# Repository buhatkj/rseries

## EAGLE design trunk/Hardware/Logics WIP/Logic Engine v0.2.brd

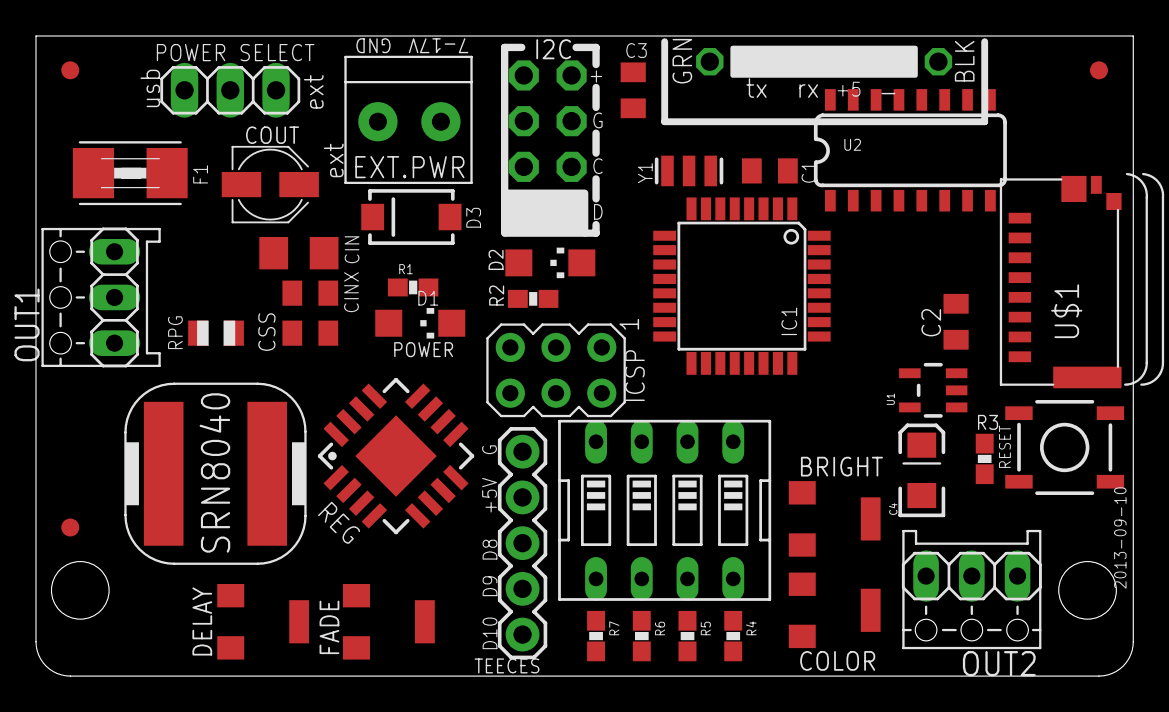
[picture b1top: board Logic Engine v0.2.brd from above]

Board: 2 copper layers, 61.0 x 35.6 mm, 45 parts (0 on the bottom side), 44 nets, no tracks yet.

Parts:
BRIGHT: 3364
C1, C2, C3: 0.1uF; C0805K
C4: 10uF; EIA3216
CIN: 10uF; C1206
CINX: 100nF; C0805K
COLOR: 3364
COUT: 22uF; CASE_B
CSS: 3.3nF; C0805K
D1: CHIPLED_1206
D2: Green; CHIPLED_1206
D3: BA340LA; SMA-DIODE
DELAY: 3364
EXT.PWR: 1X2-3.5MM
F1: 1812
FADE: 3364
FID1, FID2, FID3: FIDUCIAL1X2.5; FIDUCIAL-1X2.5
FTDI: 1X06-CLEAN
I2C, I2C1: 1X04-CB
IC1: MEGA328P; TQFP32-08
ICSP: AVRISP-6; AVRISP
INDUCTOR: SRN8040-2R2Y; SRN8040
OUT1, OUT2: MDF7_1X03
PWR_SEL1: 1X03
R1, R2: 1K; 0603-RES
R3, R4, R5, R6, R7: 10K; 0603-RES
REG: TPS62133; TPS6213X
RESET: TACTILE_SWITCH_SMD
RPG: 100k; R0805
SW1: EDG-04
TEECES: 1X05
U1: V_REG_LDOSMD; SOT23-5
U2: HEX_CONVERTER; SO016
U$1: MICROSD; MICROSD_SMALL
Y1: 16MHz; RESONATOR-SMD

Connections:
+5V: BRIGHT.3, C1.1, C2.1, COLOR.3, DELAY.3, F1.1, FADE.3, I2C.4, I2C1.4, IC1.4, IC1.6, IC1.18, ICSP.2, OUT1.2, OUT2.2, R1.1, R3.1, TEECES.2, U1.1, U1.3, U$1.4
ANALOG0: DELAY.2, IC1.23
ANALOG1: FADE.2, IC1.24
ANALOG2: BRIGHT.2, IC1.25
ANALOG3: COLOR.2, IC1.26
ANALOG4: I2C.1, I2C1.1, IC1.27
ANALOG5: I2C.2, I2C1.2, IC1.28
DIGITAL2: IC1.32, SW1.1
DIGITAL3: IC1.1, SW1.2
DIGITAL4: IC1.2, SW1.3
DIGITAL5: IC1.9, SW1.4
DIGITAL6: IC1.10, OUT1.1, OUT2.1
DIGITAL7: IC1.11, TEECES.5
DIGITAL8: IC1.12, TEECES.3
DIGITAL9: IC1.13, TEECES.4
DIGITAL10: IC1.14, U2.3
GND: BRIGHT.1, C1.2, C2.2, C4.C, CIN.2, CINX.2, COLOR.1, COUT.-, CSS.2, D1.C, D2.C, DELAY.1, EXT.PWR.1, FADE.1, FTDI.1, FTDI.2, I2C.3, I2C1.3, IC1.3, IC1.5, IC1.21, ICSP.6, OUT1.3, OUT2.3, R4.2, R5.2, R6.2, R7.2, REG.5, REG.6, REG.8, REG.15, REG.16, REG.17-THERMALPAD, RESET.3, TEECES.1, U1.2, U2.8, U$1.6, U$1.MT1, U$1.MT2, Y1.2
MISO: IC1.16, ICSP.1, U$1.7
MOSI: IC1.15, ICSP.4, U2.5
unnamed: IC1.7, Y1.1
unnamed: IC1.8, Y1.3
unnamed: INDUCTOR.P$1, REG.1
unnamed: D2.A, R2.2
unnamed: D1.A, R1.2
unnamed: CIN.1, CINX.1, D3.C, REG.10, REG.11, REG.12, REG.13
unnamed: CSS.1, REG.9
unnamed: REG.4, RPG.2
unnamed: COUT.+, INDUCTOR.P$2, PWR_SEL1.1, REG.7, REG.14, RPG.1
unnamed: F1.2, PWR_SEL1.2
unnamed: D3.A, EXT.PWR.2
unnamed: R4.1, SW1.8
unnamed: R5.1, SW1.7
unnamed: R6.1, SW1.6
unnamed: R7.1, SW1.5
unnamed: U2.4, U$1.3
unnamed: U2.6, U$1.5
unnamed: U2.2, U$1.2
unnamed: C4.A, U1.5, U2.1
RST: C3.2, IC1.29, ICSP.5, R3.2, RESET.1
RTS#: C3.1, FTDI.6
RXD: FTDI.4, IC1.30
SCK: IC1.17, ICSP.3, R2.1, U2.7
TXD: FTDI.5, IC1.31
USB_5V: FTDI.3, PWR_SEL1.3

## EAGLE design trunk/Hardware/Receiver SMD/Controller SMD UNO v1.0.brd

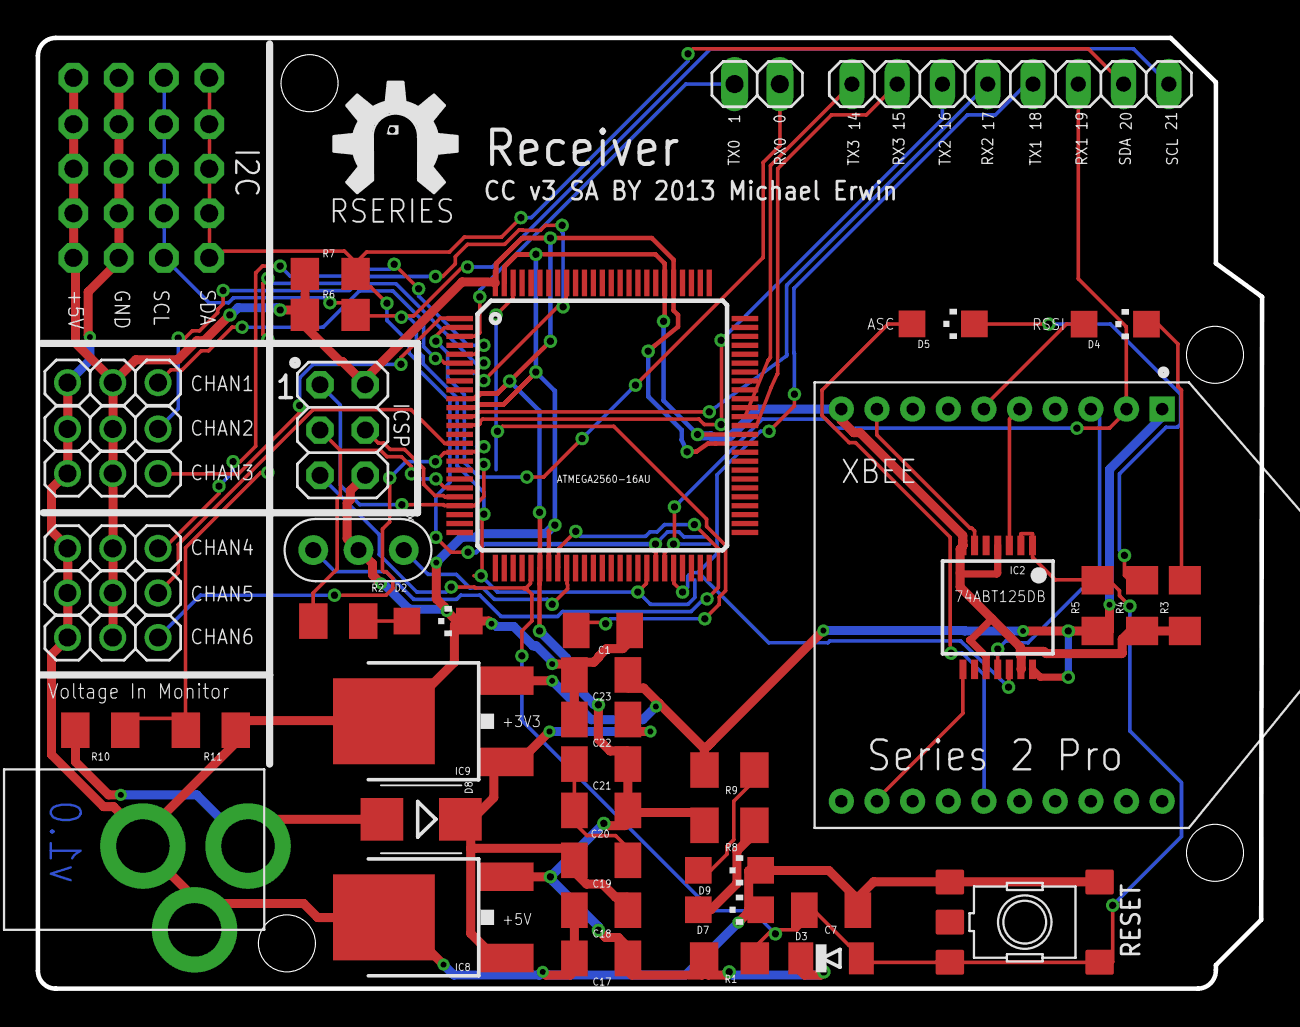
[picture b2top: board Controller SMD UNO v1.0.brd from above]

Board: 2 copper layers, 68.7 x 53.3 mm, 51 parts (1 on the bottom side), 41 nets.

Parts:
C1, C17, C18, C21, C23: 0.1uF; C1206K
C7: 22p; C1206K
C19, C20, C22: 10uf 25V; C1206K
CHAN1, CHAN2, CHAN3, CHAN4, CHAN5, CHAN6: 1X03
COMMUNICATION: 8x1F-H8.5; 1X08
D2: RED; CHIPLED_1206
D3: CD1206-S01575; MINIMELF
D4, D5, D7, D9: CHIPLED_1206
D8: SMB
I2C, I2C1, I2C2, I2C3, I2C4: 1X04-CB
IC2: 74ABT125DB; SSOP14
IC3: ATMEGA2560-16AU; TQFP100
IC8, IC9: LM2931_FIXED; DPAK
ICSP: 3x2M; 2X03
J2: 2.1MMJACK; PJ-102A
JP1: 1X02
R1, R5, R6, R7: 10K; R1206
R2, R8, R9: 1.0 K; M1206
R3, R4: 1K; R1206
R10: 47.0 K; M1206
R11: 24.0 K; M1206
RESET: TS42031-160R-TR-7260; TS42
U$1: ROYAL-ENGINEERS-OF-NABOO
U$3: RSERIES-OSHW-LOGO; RSERIES-OSHW-LOGO-LARGE
X1: 16.00MHz; CERM_OSC
XBEE: XBEE

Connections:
+5V: C17.1, C20.1, C21.1, CHAN1.2, CHAN2.2, CHAN3.2, CHAN4.2, CHAN5.2, CHAN6.2, D3.C, I2C.4, I2C1.4, I2C2.4, I2C3.4, I2C4.4, IC3.10, IC3.31, IC3.61, IC3.80, IC3.100, IC8.3, ICSP.2, R1.1, R6.2, R7.2, R8.1
+9V: C18.1, C19.1, C22.1, D8.C, IC8.1, IC9.1
ADC5: IC3.92, R10.1, R11.2
AREF: C1.1, IC3.98
GND: C1.2, C7.2, C17.2, C18.2, C22.2, C23.2, CHAN1.3, CHAN2.3, CHAN3.3, CHAN4.3, CHAN5.3, CHAN6.3, D2.C, D7.C, D9.C, I2C.3, I2C1.3, I2C2.3, I2C3.3, I2C4.3, IC2.4, IC2.7, IC2.10, IC2.13, IC3.11, IC3.32, IC3.62, IC3.81, IC3.99, IC8.4, IC9.4, ICSP.6, J2.RING, J2.RING_SW, R3.1, R4.1, R11.1, RESET.1, RESET.2, X1.P$2, XBEE.10
unnamed: IC2.11, XBEE.3
unnamed: D5.C, R4.2
unnamed: D4.A, XBEE.6
unnamed: D4.C, R3.2
unnamed: D9.A, R9.2
unnamed: IC2.6, XBEE.9
unnamed: D2.A, R2.1
unnamed: IC2.3, XBEE.5
unnamed: IC2.8, XBEE.12
unnamed: D5.A, XBEE.15
unnamed: D7.A, R8.2
unnamed: D8.A, J2.TIP, R10.2
unnamed: C19.2, C20.2, C21.2
PB1: IC3.20, ICSP.3, R2.2
PB2: IC3.21, ICSP.4
PB3: IC3.22, ICSP.1
PE0: IC3.2, JP1.1
PE1: IC3.3, JP1.2
PE3: CHAN4.1, IC3.5
PE4: CHAN1.1, IC3.6
PE5: CHAN2.1, IC3.7
PG5: CHAN3.1, IC3.1
PH3: CHAN5.1, IC3.15
PH4: CHAN6.1, IC3.16
RESET: C7.1, D3.A, IC2.1, IC2.2, IC3.30, ICSP.5, R1.2, R5.2, RESET.3, RESET.4
RXD1: COMMUNICATION.3, IC3.45, XBEE.2
RXD2: COMMUNICATION.5, IC3.12
RXD3: COMMUNICATION.7, IC3.63
SCL: COMMUNICATION.1, I2C.2, I2C1.2, I2C2.2, I2C3.2, I2C4.2, IC3.43, R6.1
SDA: COMMUNICATION.2, I2C.1, I2C1.1, I2C2.1, I2C3.1, I2C4.1, IC3.44, R7.1
TXD1: COMMUNICATION.4, IC2.12, IC3.46
TXD2: COMMUNICATION.6, IC3.13
TXD3: COMMUNICATION.8, IC3.64
VCC: C23.1, IC2.14, IC9.3, R5.1, R9.1, XBEE.1
XTAL1: IC3.34, X1.P$3
XTAL2: IC3.33, X1.P$1

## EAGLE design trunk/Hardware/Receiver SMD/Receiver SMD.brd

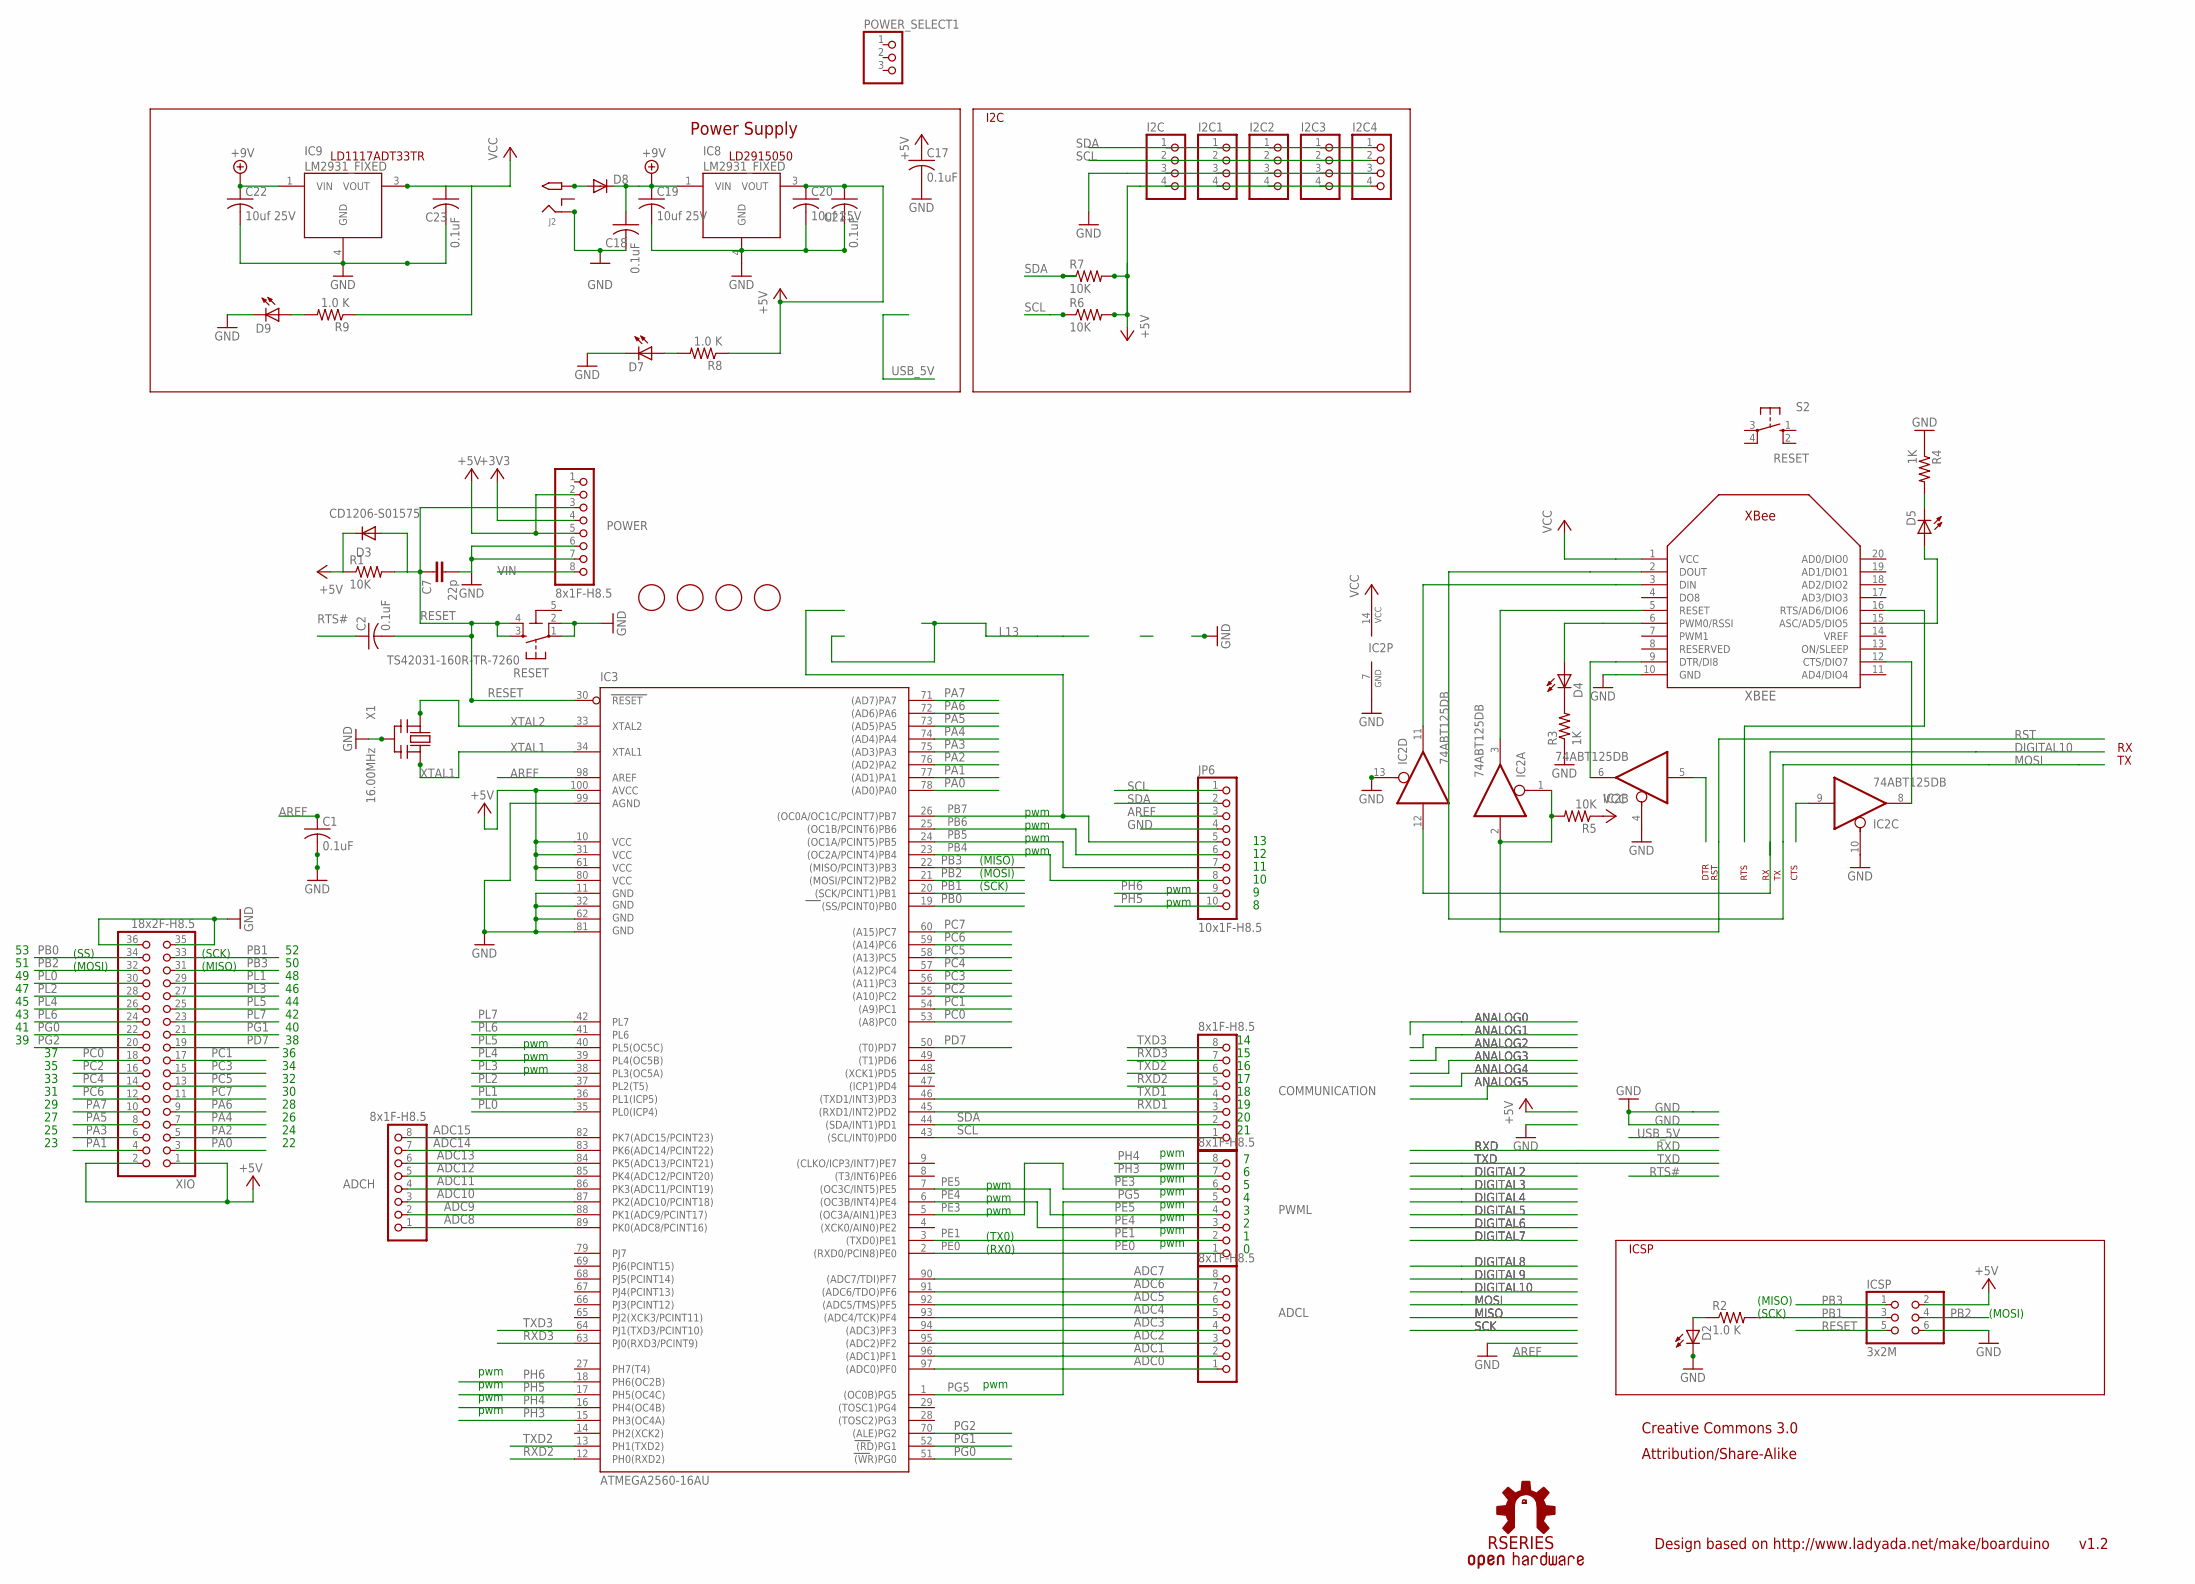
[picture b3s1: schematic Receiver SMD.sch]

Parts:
ADCH: 8x1F-H8.5; 1X08
ADCL: 8x1F-H8.5; 1X08
C1, C2, C17, C18, C21, C23: 0.1uF; C1206K
C7: 22p; C0603-ROUND
C19, C20, C22: 10uf 25V; C1206K
COMMUNICATION: 8x1F-H8.5; 1X08
D2: RED; CHIPLED_1206
D3: CD1206-S01575; MINIMELF
D4, D5, D7, D9: LEDCHIPLED_1206; CHIPLED_1206
D8: DIODE-SMB; SMB
FD1, FD2, FD3, FD4: FIDUCIALMOUNT; FIDUCIA-MOUNT
I2C, I2C1, I2C2, I2C3, I2C4: PINHD-1X4CB; 1X04-CB
IC2: 74ABT125DB; SSOP14
IC3: ATMEGA2560-16AU; TQFP100
IC8, IC9: LM2931_FIXED; DPAK
ICSP: 3x2M; 2X03
J2: 2.1MMJACK; PJ-102A
JP6: 10x1F-H8.5; 1X10
POWER: 8x1F-H8.5; 1X08
POWER_SELECT1: PINHD-1X3; 1X03
PWML: 8x1F-H8.5; 1X08
R1, R5, R6, R7: 10K; R1206
R2, R8, R9: 1.0 K; M1206
R3, R4: 1K; R1206
RESET: TS42031-160R-TR-7260; TS42
S2: RESET; B3F-10XX
U$6: RSERIES-OSHW-LOGOMEDIUM; RSERIES-OSHW-LOGO-MEDIUM
X1: 16.00MHz; CERM_OSC
XBEE: XBEE
XIO: 18x2F-H8.5; 2X18

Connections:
5-GND: RESET.5 (5-GND)
+3V3: POWER.4
+5V: C17.1, C20.1, C21.1, D3.C, I2C.4, I2C1.4, I2C2.4, I2C3.4, I2C4.4, IC3.10 (VCC), IC3.31 (VCC1), IC3.61 (VCC2), IC3.80 (VCC3), IC3.100 (AVCC), IC8.3 (VOUT), ICSP.2, POWER.2, POWER.5, R1.1, R6.2, R7.2, R8.1, XIO.1, XIO.2
+9V: C18.1, C19.1, C22.1, D8.C, IC8.1 (VIN), IC9.1 (VIN)
ADC0: ADCL.1, IC3.97 ((ADC0)PF0)
ADC1: ADCL.2, IC3.96 ((ADC1)PF1)
ADC2: ADCL.3, IC3.95 ((ADC2)PF2)
ADC3: ADCL.4, IC3.94 ((ADC3)PF3)
ADC4: ADCL.5, IC3.93 ((ADC4/TCK)PF4)
ADC5: ADCL.6, IC3.92 ((ADC5/TMS)PF5)
ADC6: ADCL.7, IC3.91 ((ADC6/TDO)PF6)
ADC7: ADCL.8, IC3.90 ((ADC7/TDI)PF7)
ADC8: ADCH.1, IC3.89 (PK0(ADC8/PCINT16))
ADC9: ADCH.2, IC3.88 (PK1(ADC9/PCINT17))
ADC10: ADCH.3, IC3.87 (PK2(ADC10/PCINT18))
ADC11: ADCH.4, IC3.86 (PK3(ADC11/PCINT19))
ADC12: ADCH.5, IC3.85 (PK4(ADC12/PCINT20))
ADC13: ADCH.6, IC3.84 (PK5(ADC13/PCINT21))
ADC14: ADCH.7, IC3.83 (PK6(ADC14/PCINT22))
ADC15: ADCH.8, IC3.82 (PK7(ADC15/PCINT23))
AREF: C1.1, IC3.98 (AREF), JP6.3
DIGITAL10: IC2.12 (I)
GND: C1.2, C7.2, C17.2, C18.2, C22.2, C23.2, D2.C, D7.C, D9.C, I2C.3, I2C1.3, I2C2.3, I2C3.3, I2C4.3, IC2.4 (OE), IC2.7 (GND), IC2.10 (OE), IC2.13 (OE), IC3.11 (GND), IC3.32 (GND1), IC3.62 (GND2), IC3.81 (GND3), IC3.99 (AGND), IC8.4 (GND), IC9.4 (GND), ICSP.6, J2.RING, JP6.4, POWER.6, POWER.7, R3.1, R4.1, RESET.1, RESET.2, X1.P$2 (GND), XBEE.10 (GND), XIO.35, XIO.36
MOSI: XBEE.2 (DOUT)
unnamed: IC2.11 (O), XBEE.3 (DIN)
unnamed: D5.C, R4.2
unnamed: D4.A, XBEE.6 (PWM0/RSSI)
unnamed: D4.C, R3.2
unnamed: D9.A, R9.2
unnamed: IC2.6 (O), XBEE.9 (DTR/DI8)
unnamed: D2.A, R2.1
unnamed: IC2.3 (O), XBEE.5 (RESET)
unnamed: IC2.8 (O), XBEE.12 (CTS/DIO7)
unnamed: D5.A, XBEE.15 (ASC/AD5/DIO5)
unnamed: D7.A, R8.2
unnamed: D8.A, J2.TIP
unnamed: C19.2, C20.2, C21.2
PA0: IC3.78 ((AD0)PA0), XIO.3
PA1: IC3.77 ((AD1)PA1), XIO.4
PA2: IC3.76 ((AD2)PA2), XIO.5
PA3: IC3.75 ((AD3)PA3), XIO.6
PA4: IC3.74 ((AD4)PA4), XIO.7
PA5: IC3.73 ((AD5)PA5), XIO.8
PA6: IC3.72 ((AD6)PA6), XIO.9
PA7: IC3.71 ((AD7)PA7), XIO.10
PB0: IC3.19 ((SS/PCINT0)PB0), XIO.34
PB1: IC3.20 ((SCK/PCINT1)PB1), ICSP.3, R2.2, XIO.33
PB2: IC3.21 ((MOSI/PCINT2)PB2), ICSP.4, XIO.32
PB3: IC3.22 ((MISO/PCINT3)PB3), ICSP.1, XIO.31
PB4: IC3.23 ((OC2A/PCINT4)PB4), JP6.8
PB5: IC3.24 ((OC1A/PCINT5)PB5), JP6.7
PB6: IC3.25 ((OC1B/PCINT6)PB6), JP6.6
PB7: IC3.26 ((OC0A/OC1C/PCINT7)PB7), JP6.5
PC0: IC3.53 ((A8)PC0), XIO.18
PC1: IC3.54 ((A9)PC1), XIO.17
PC2: IC3.55 ((A10)PC2), XIO.16
PC3: IC3.56 ((A11)PC3), XIO.15
PC4: IC3.57 ((A12)PC4), XIO.14
PC5: IC3.58 ((A13)PC5), XIO.13
PC6: IC3.59 ((A14)PC6), XIO.12
PC7: IC3.60 ((A15)PC7), XIO.11
PD7: IC3.50 ((T0)PD7), XIO.19
PE0: IC3.2 ((RXD0/PCIN8)PE0), PWML.1
PE1: IC3.3 ((TXD0)PE1), PWML.2
PE3: IC3.5 ((OC3A/AIN1)PE3), PWML.6
PE4: IC3.6 ((OC3B/INT4)PE4), PWML.3
PE5: IC3.7 ((OC3C/INT5)PE5), PWML.4
PG0: IC3.51 ((WR)PG0), XIO.22
PG1: IC3.52 ((RD)PG1), XIO.21
PG2: IC3.70 ((ALE)PG2), XIO.20
PG5: IC3.1 ((OC0B)PG5), PWML.5
PH3: IC3.15 (PH3(OC4A)), PWML.7
PH4: IC3.16 (PH4(OC4B)), PWML.8
PH5: IC3.17 (PH5(OC4C)), JP6.10
PH6: IC3.18 (PH6(OC2B)), JP6.9
PL0: IC3.35 (PL0(ICP4)), XIO.30
PL1: IC3.36 (PL1(ICP5)), XIO.29
PL2: IC3.37 (PL2(T5)), XIO.28
PL3: IC3.38 (PL3(OC5A)), XIO.27
PL4: IC3.39 (PL4(OC5B)), XIO.26
PL5: IC3.40 (PL5(OC5C)), XIO.25
PL6: IC3.41 (PL6), XIO.24
PL7: IC3.42 (PL7), XIO.23
RESET: C2.2, C7.1, D3.A, IC3.30 (RESET), ICSP.5, POWER.3, R1.2, RESET.3, RESET.4
RST: IC2.1 (OE), IC2.2 (I), R5.2
RTS: XBEE.16 (RTS/AD6/DIO6)
RTS#: C2.1
RXD1: COMMUNICATION.3, IC3.45 ((RXD1/INT2)PD2)
RXD2: COMMUNICATION.5, IC3.12 (PH0(RXD2))
RXD3: COMMUNICATION.7, IC3.63 (PJ0(RXD3/PCINT9))
SCL: COMMUNICATION.1, I2C.2, I2C1.2, I2C2.2, I2C3.2, I2C4.2, IC3.43 ((SCL/INT0)PD0), JP6.1, R6.1
SDA: COMMUNICATION.2, I2C.1, I2C1.1, I2C2.1, I2C3.1, I2C4.1, IC3.44 ((SDA/INT1)PD1), JP6.2, R7.1
TXD1: COMMUNICATION.4, IC3.46 ((TXD1/INT3)PD3)
TXD2: COMMUNICATION.6, IC3.13 (PH1(TXD2))
TXD3: COMMUNICATION.8, IC3.64 (PJ1(TXD3/PCINT10))
VCC: C23.1, IC2.14 (VCC), IC9.3 (VOUT), R5.1, R9.1, XBEE.1 (VCC)
VIN: POWER.8
XTAL1: IC3.34 (XTAL1), X1.P$3 (OUT)
XTAL2: IC3.33 (XTAL2), X1.P$1 (IN)

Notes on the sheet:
(SCK)
(MISO)
(MOSI)
pwm
(TX0)
(RX0)
(SS)
DTR
RST
RTS
CTS
v1.2
Design based on http://www.ladyada.net/make/boarduino
Creative Commons 3.0
Attribution/Share-Alike
I2C
ICSP
Power Supply
LD2915050
LD1117ADT33TR

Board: 2 copper layers, 54 parts (0 on the bottom side), 92 nets, no tracks yet.

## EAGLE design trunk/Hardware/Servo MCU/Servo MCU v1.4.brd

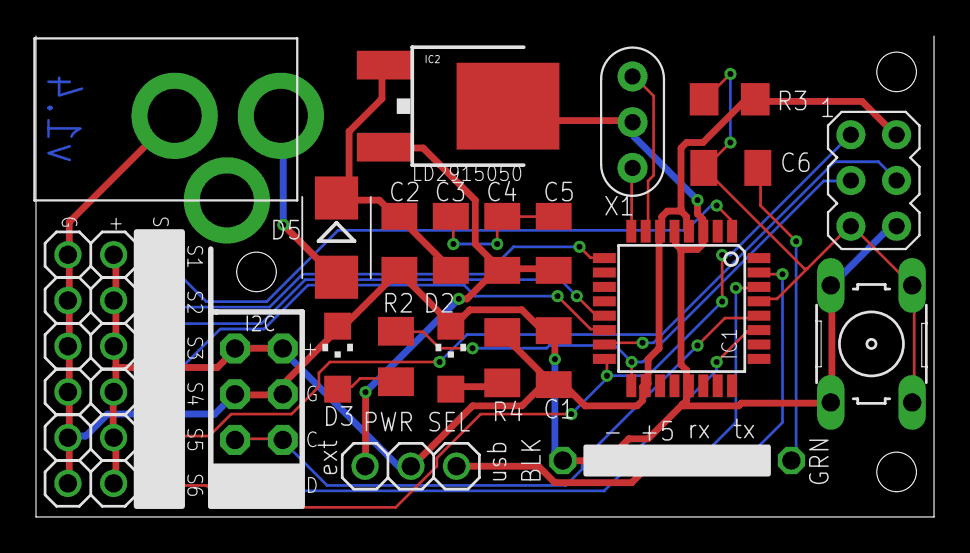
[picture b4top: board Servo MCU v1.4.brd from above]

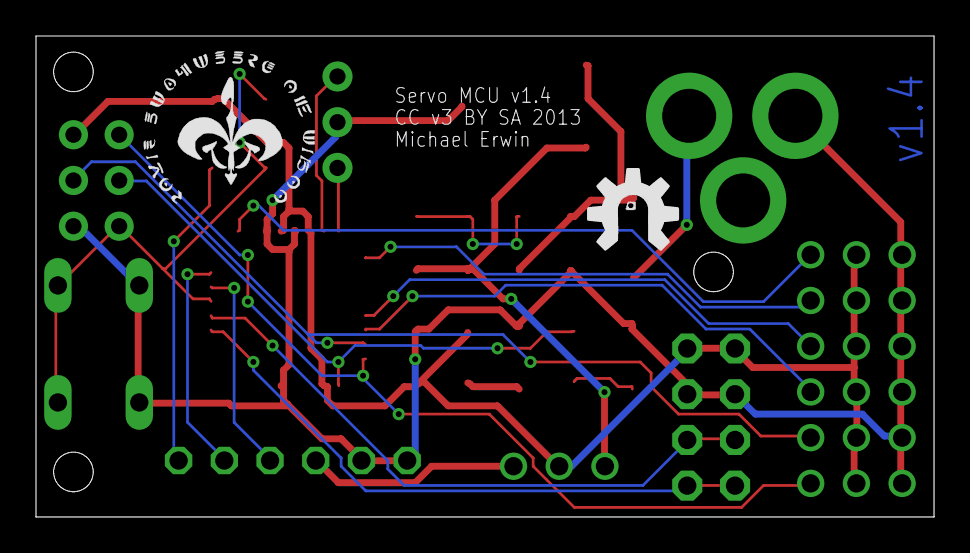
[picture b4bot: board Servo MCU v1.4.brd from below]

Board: 2 copper layers, 49.9 x 26.7 mm, 30 parts (2 on the bottom side), 24 nets.

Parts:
C1, C2, C5, C6: 0.1uF; C1206K
C3, C4: 10uf 25V; C1206K
D2: CHIPLED_1206
D3: Green; CHIPLED_1206
D5: SMB
I2C, I2C1: 1X04-CB
IC1: MEGA48/88/168-AU; TQFP32-08
IC2: LM2931_FIXED; DPAK
ICSP: AVRISP-6; AVRISP
J2: 2.1MMJACK; PJ-102A
JP1, JP2, JP3, JP4, JP5, JP6: 1X03
JP7: 1X06-CLEAN
PWR_SELECT: 1X03
R1: 10K; R1206
R3, R4: 1.0 K; M1206
S1: RESET; B3F-10XX
U$2: RSERIES-OSHW-LOGOMEDIUM; RSERIES-OSHW-LOGO-MEDIUM
U$3: ROYAL-ENGINEERS-OF-NABOOSMALL; ROYAL-ENGINEERS-OF-NABOO-SMALL
X1: 16.00MHz; CERM_OSC

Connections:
+5V: C1.1, I2C.4, I2C1.4, IC1.4, IC1.6, IC1.18, ICSP.2, JP1.2, JP2.2, JP3.2, JP4.2, JP5.2, JP6.2, PWR_SELECT.2, R1.1, R4.1
+9V: C2.1, C3.1, D5.C, IC2.1
ANALOG4: I2C.1, I2C1.1, IC1.27
ANALOG5: I2C.2, I2C1.2, IC1.28
DIGITAL3: IC1.1, JP1.1
DIGITAL5: IC1.9, JP2.1
DIGITAL9: IC1.13, JP3.1
DIGITAL10: IC1.14, JP4.1
GND: C1.2, C2.2, D2.C, D3.C, I2C.3, I2C1.3, IC1.3, IC1.5, IC1.21, IC2.4, ICSP.6, J2.RING, JP1.3, JP2.3, JP3.3, JP4.3, JP5.3, JP6.3, JP7.1, JP7.2, S1.1, S1.2, X1.P$2
MISO: IC1.16, ICSP.1, JP6.1
MOSI: IC1.15, ICSP.4, JP5.1
unnamed: IC1.7, X1.P$1
unnamed: IC1.8, X1.P$3
unnamed: D3.A, R3.2
unnamed: D2.A, R4.2
unnamed: D5.A, J2.TIP
unnamed: C3.2, C4.2, C5.2
unnamed: C4.1, C5.1, IC2.3, PWR_SELECT.1
RST: C6.2, IC1.29, ICSP.5, R1.2, S1.3, S1.4
RTS#: C6.1, JP7.6
RXD: IC1.30, JP7.4
SCK: IC1.17, ICSP.3, R3.1
TXD: IC1.31, JP7.5
USB_5V: JP7.3, PWR_SELECT.3

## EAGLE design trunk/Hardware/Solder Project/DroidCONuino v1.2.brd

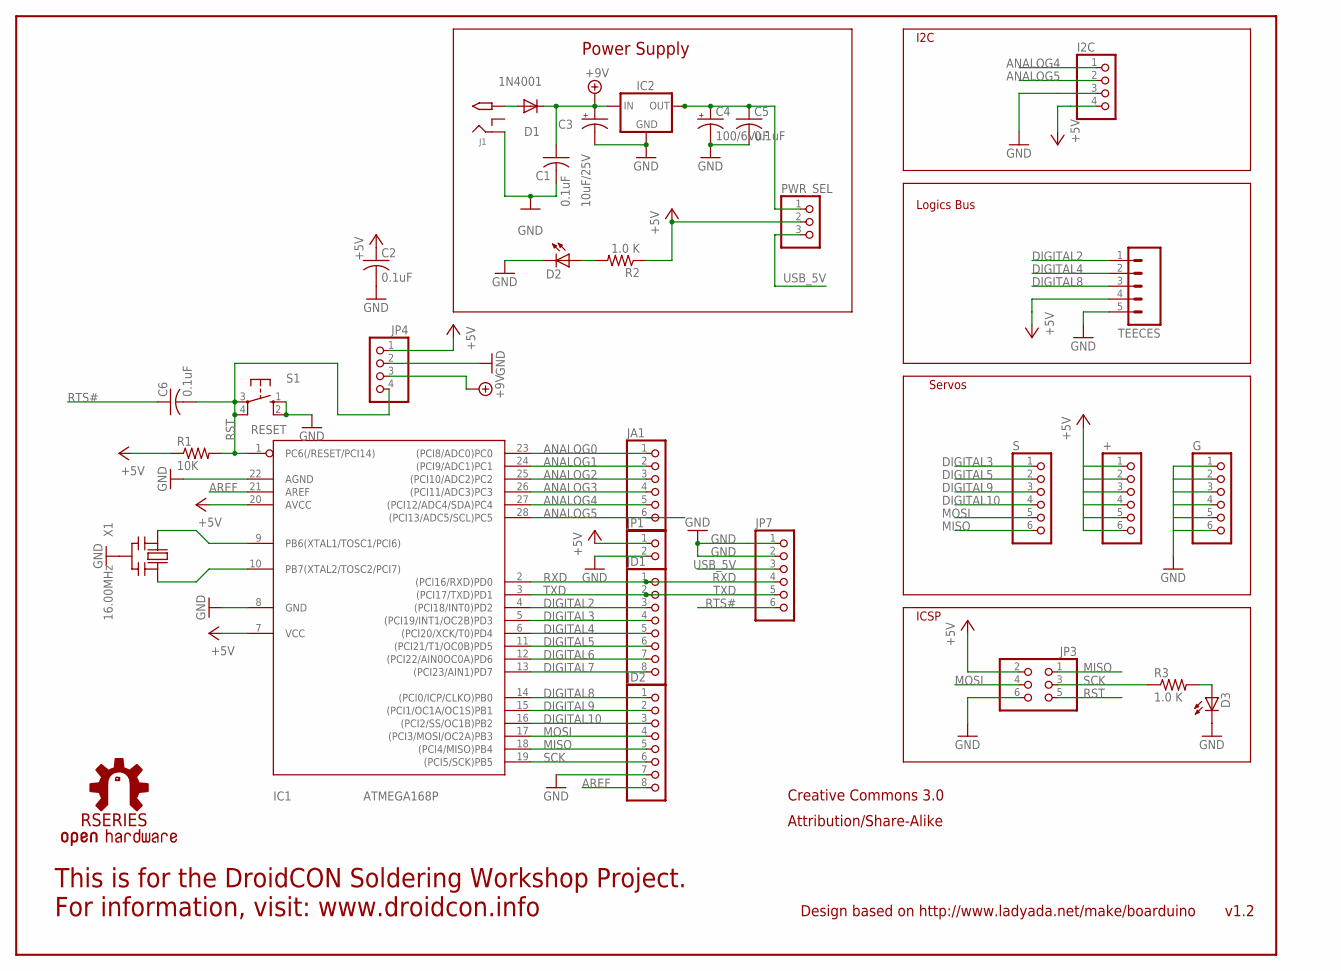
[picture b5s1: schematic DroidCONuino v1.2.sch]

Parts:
+: PINHD-1X6CLEAN; 1X06-CLEAN
C1, C2, C5, C6: 0.1uF; C025-025X050
C3: 10uF/25V; E2,5-6
C4: 100/6VuF; E2,5-6
D1: 1N4001; DO41-10
D2: LED3MM
D3: Green; LED3MM
G: PINHD-1X6CLEAN; 1X06-CLEAN
I2C: PINHD-1X4CB; 1X04-CB
IC1: ATMEGA168P; DIL28/3
IC2: 78XXS
J1: 2.1MMJACK; PJ-102A
JA1: PINHD-1X6CB; 1X06-CLEANBIG
JD1, JD2: PINHD-1X8CLEANBIG; 1X08-CLEANBIG
JP1: PINHD-1X2CB; 1X02-CB
JP3: PINHD-2X3; 2X03
JP4: PINHD-1X4CB; 1X04-CB
JP7: PINHD-1X6CLEAN; 1X06-CLEAN
PWR_SEL: PINHD-1X3; 1X03
R1: 10K; 0207/5V
R2, R3: 1.0 K; 0207/5V
S: PINHD-1X6CLEAN; 1X06-CLEAN
S1: RESET; B3F-10XX
TEECES: M05PTH; 1X05
U$2: RSERIES-OSHW-LOGOMEDIUM; RSERIES-OSHW-LOGO-MEDIUM
X1: 16.00MHz; CERM_OSC

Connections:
+5V: +.1, +.2, +.3, +.4, +.5, +.6, C2.1, I2C.4, IC1.7 (VCC), IC1.20 (AVCC), JP1.1, JP3.2, JP4.1, PWR_SEL.2, R1.1, R2.1, TEECES.4
+9V: C1.1, C3.+, D1.C, IC2.IN, JP4.3
ANALOG0: IC1.23 ((PCI8/ADC0)PC0), JA1.1
ANALOG1: IC1.24 ((PCI9/ADC1)PC1), JA1.2
ANALOG2: IC1.25 ((PCI10/ADC2)PC2), JA1.3
ANALOG3: IC1.26 ((PCI11/ADC3)PC3), JA1.4
ANALOG4: I2C.1, IC1.27 ((PCI12/ADC4/SDA)PC4), JA1.5
ANALOG5: I2C.2, IC1.28 ((PCI13/ADC5/SCL)PC5), JA1.6
AREF: IC1.21 (AREF), JD2.8
DIGITAL2: IC1.4 ((PCI18/INT0)PD2), JD1.3, TEECES.1
DIGITAL3: IC1.5 ((PCI19/INT1/OC2B)PD3), JD1.4, S.1
DIGITAL4: IC1.6 ((PCI20/XCK/T0)PD4), JD1.5, TEECES.2
DIGITAL5: IC1.11 ((PCI21/T1/OC0B)PD5), JD1.6, S.2
DIGITAL6: IC1.12 ((PCI22/AIN0OC0A)PD6), JD1.7
DIGITAL7: IC1.13 ((PCI23/AIN1)PD7), JD1.8
DIGITAL8: IC1.14 ((PCI0/ICP/CLKO)PB0), JD2.1, TEECES.3
DIGITAL9: IC1.15 ((PCI1/OC1A/OC1S)PB1), JD2.2, S.3
DIGITAL10: IC1.16 ((PCI2/SS/OC1B)PB2), JD2.3, S.4
GND: C1.2, C2.2, C3.-, C4.-, C5.2, D2.K (C), D3.K (C), G.1, G.2, G.3, G.4, G.5, G.6, I2C.3, IC1.8 (GND), IC1.22 (AGND), IC2.GND, J1.RING, JD2.7, JP1.2, JP3.6, JP4.2, JP7.1, JP7.2, S1.1 (S), S1.2 (S1), TEECES.5, X1.P$2 (GND)
MISO: IC1.18 ((PCI4/MISO)PB4), JD2.5, JP3.1, S.6
MOSI: IC1.17 ((PCI3/MOSI/OC2A)PB3), JD2.4, JP3.4, S.5
unnamed: IC1.9 (PB6(XTAL1/TOSC1/PCI6)), X1.P$1 (IN)
unnamed: IC1.10 (PB7(XTAL2/TOSC2/PCI7)), X1.P$3 (OUT)
unnamed: D2.A, R2.2
unnamed: D3.A, R3.2
unnamed: D1.A, J1.TIP
unnamed: C4.+, C5.1, IC2.OUT, PWR_SEL.1
RST: C6.2, IC1.1 (PC6(/RESET/PCI14)), JP3.5, JP4.4, R1.2, S1.3, S1.4 (P1)
RTS#: C6.1, JP7.6
RXD: IC1.2 ((PCI16/RXD)PD0), JD1.1, JP7.4
SCK: IC1.19 ((PCI5/SCK)PB5), JD2.6, JP3.3, R3.1
TXD: IC1.3 ((PCI17/TXD)PD1), JD1.2, JP7.5
USB_5V: JP7.3, PWR_SEL.3

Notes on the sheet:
Power Supply
v1.2
Design based on http://www.ladyada.net/make/boarduino
Creative Commons 3.0
Attribution/Share-Alike
Servos
Logics Bus
I2C
ICSP
This is for the DroidCON Soldering Workshop Project. For information, visit: www.droidcon.info

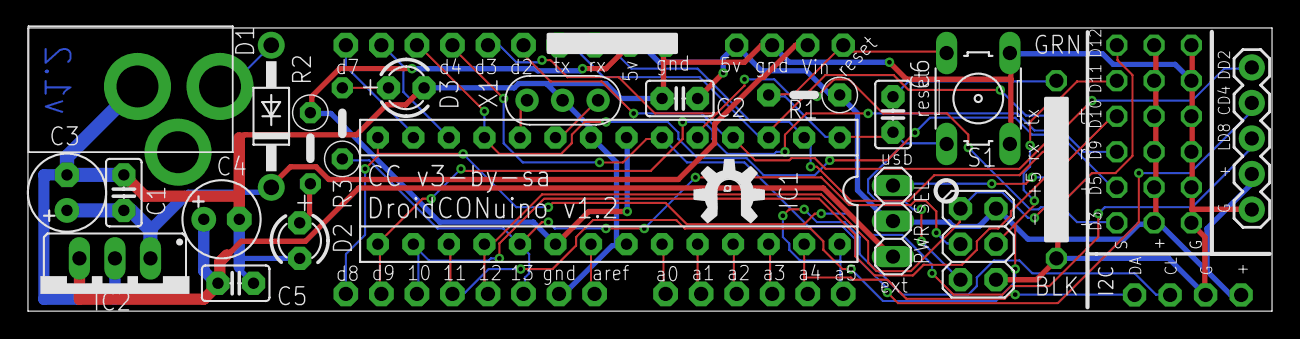
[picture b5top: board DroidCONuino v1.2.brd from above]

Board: 2 copper layers, 88.9 x 20.2 mm, 31 parts (0 on the bottom side), 33 nets.

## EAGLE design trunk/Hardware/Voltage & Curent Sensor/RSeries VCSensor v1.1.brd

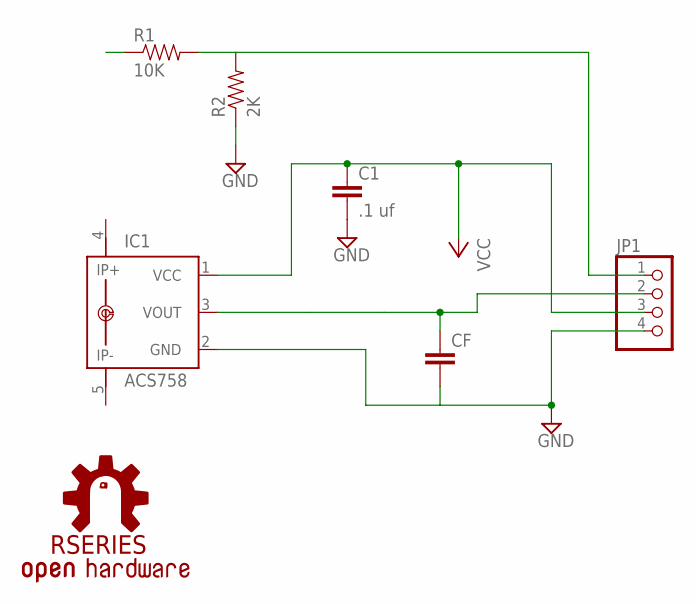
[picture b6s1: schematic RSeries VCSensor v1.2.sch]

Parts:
C1: .1 uf; CAP-PTH-SMALL
CF: CAPPTH1; CAP-PTH-5MM
IC1: ACS758; CB-PFF
JP1: PINHD-1X4; 1X04
R1: 10K; AXIAL-0.4
R2: 2K; AXIAL-0.4
U$1: RSERIES-OSHW-LOGO; RSERIES-OSHW-LOGO-LARGE

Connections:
GND: C1.2, CF.2, IC1.2 (GND), JP1.4, R2.P$1 (1)
unnamed: CF.1, IC1.3 (VOUT), JP1.2
unnamed: JP1.1, R1.P$2 (2), R2.P$2 (2)
VCC: C1.1, IC1.1 (VCC), JP1.3

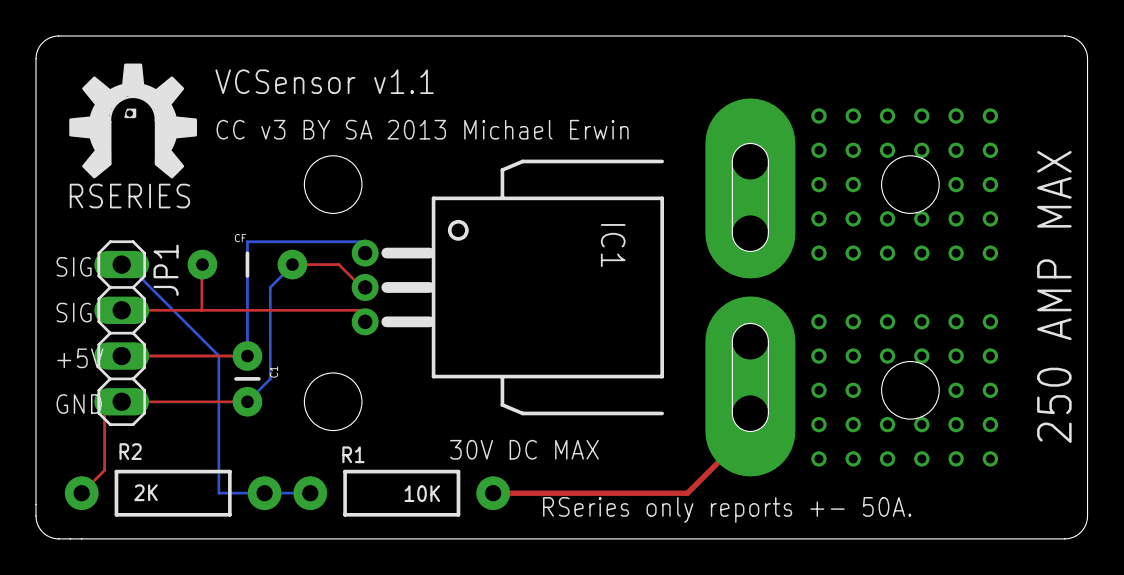
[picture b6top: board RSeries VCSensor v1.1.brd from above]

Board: 2 copper layers, 58.4 x 27.9 mm, 8 parts (1 on the bottom side), 4 nets.

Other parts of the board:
U$3: ROYAL-ENGINEERS-OF-NABOO-SMALL

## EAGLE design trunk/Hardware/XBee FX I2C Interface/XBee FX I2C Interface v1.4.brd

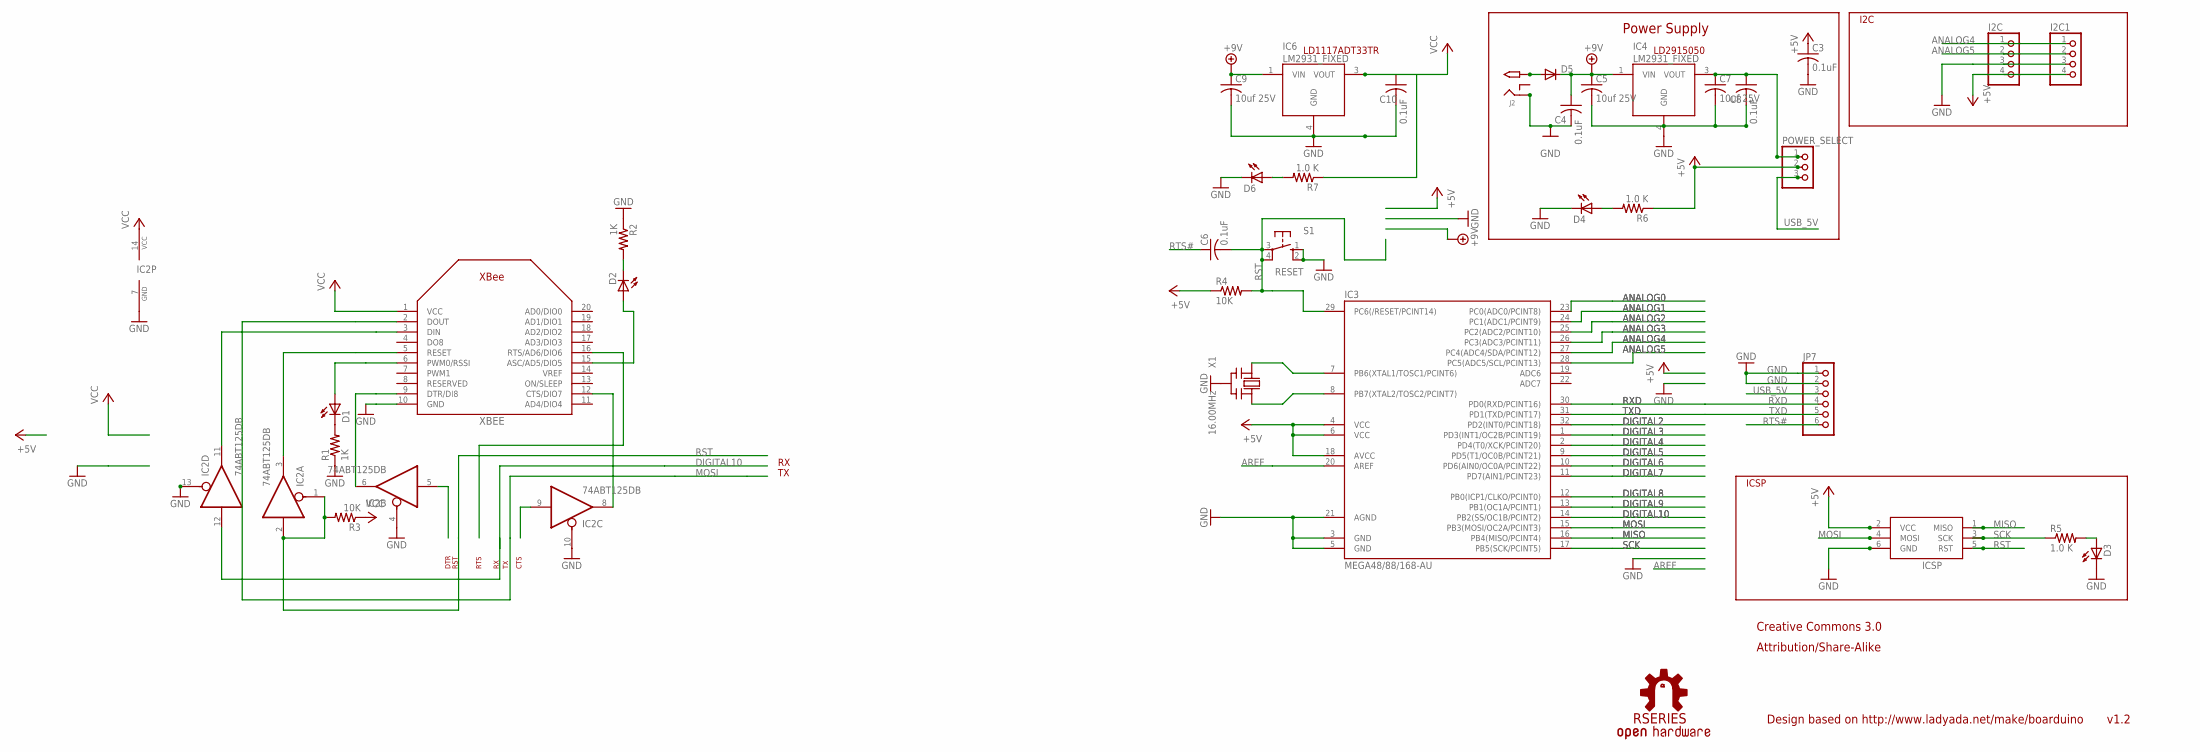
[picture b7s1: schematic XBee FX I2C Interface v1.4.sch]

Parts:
C3, C4, C6, C8, C10: 0.1uF; C1206K
C5, C7, C9: 10uf 25V; C1206K
D1, D2, D4, D6: LEDCHIPLED_1206; CHIPLED_1206
D3: RED; CHIPLED_1206
D5: DIODE-SMB; SMB
I2C, I2C1: PINHD-1X4CB; 1X04-CB
IC2: 74ABT125DB; SSOP14
IC3: MEGA48/88/168-AU; TQFP32-08
IC4, IC6: LM2931_FIXED; DPAK
ICSP: AVRISP-6; AVRISP
J2: 2.1MMJACK; PJ-102A
JP7: PINHD-1X6CLEAN; 1X06-CLEAN
POWER_SELECT: PINHD-1X3; 1X03
R1, R2: 1K; R1206
R3, R4: 10K; R1206
R5, R6, R7: 1.0 K; M1206
S1: RESET; B3F-10XX
U$6: RSERIES-OSHW-LOGOMEDIUM; RSERIES-OSHW-LOGO-MEDIUM
X1: 16.00MHz; CERM_OSC
XBEE: XBEE

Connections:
+5V: C3.1, I2C.4, I2C1.4, IC3.4 (VCC), IC3.6 (VCC), IC3.18 (AVCC), ICSP.2 (VCC), POWER_SELECT.2, R4.1, R6.1
+9V: C4.1, C5.1, C9.1, D5.C, IC4.1 (VIN), IC6.1 (VIN)
ANALOG0: IC3.23 (PC0(ADC0/PCINT8))
ANALOG1: IC3.24 (PC1(ADC1/PCINT9))
ANALOG2: IC3.25 (PC2(ADC2/PCINT10))
ANALOG3: IC3.26 (PC3(ADC3/PCINT11))
ANALOG4: I2C.1, I2C1.1, IC3.27 (PC4(ADC4/SDA/PCINT12))
ANALOG5: I2C.2, I2C1.2, IC3.28 (PC5(ADC5/SCL/PCINT13))
AREF: IC3.20 (AREF)
DIGITAL2: IC3.32 (PD2(INT0/PCINT18))
DIGITAL3: IC3.1 (PD3(INT1/OC2B/PCINT19))
DIGITAL4: IC3.2 (PD4(T0/XCK/PCINT20))
DIGITAL5: IC3.9 (PD5(T1/OC0B/PCINT21))
DIGITAL6: IC3.10 (PD6(AIN0/OC0A/PCINT22))
DIGITAL7: IC3.11 (PD7(AIN1/PCINT23))
DIGITAL8: IC3.12 (PB0(ICP1/CLKO/PCINT0))
DIGITAL9: IC3.13 (PB1(OC1A/PCINT1))
DIGITAL10: IC2.12 (I), IC3.14 (PB2(SS/OC1B/PCINT2))
GND: C3.2, C4.2, C9.2, C10.2, D3.C, D4.C, D6.C, I2C.3, I2C1.3, IC2.4 (OE), IC2.7 (GND), IC2.10 (OE), IC2.13 (OE), IC3.3 (GND), IC3.5 (GND), IC3.21 (AGND), IC4.4 (GND), IC6.4 (GND), ICSP.6 (GND), J2.RING, JP7.1, JP7.2, R1.1, R2.1, S1.1 (S), S1.2 (S1), X1.P$2 (GND), XBEE.10 (GND)
MISO: IC3.16 (PB4(MISO/PCINT4)), ICSP.1 (MISO)
MOSI: IC3.15 (PB3(MOSI/OC2A/PCINT3)), ICSP.4 (MOSI), XBEE.2 (DOUT)
unnamed: IC2.11 (O), XBEE.3 (DIN)
unnamed: D2.C, R2.2
unnamed: D6.A, R7.2
unnamed: D1.A, XBEE.6 (PWM0/RSSI)
unnamed: D1.C, R1.2
unnamed: IC2.6 (O), XBEE.9 (DTR/DI8)
unnamed: IC2.3 (O), XBEE.5 (RESET)
unnamed: IC2.8 (O), XBEE.12 (CTS/DIO7)
unnamed: D2.A, XBEE.15 (ASC/AD5/DIO5)
unnamed: IC3.7 (PB6(XTAL1/TOSC1/PCINT6)), X1.P$1 (IN)
unnamed: IC3.8 (PB7(XTAL2/TOSC2/PCINT7)), X1.P$3 (OUT)
unnamed: D3.A, R5.2
unnamed: D4.A, R6.2
unnamed: D5.A, J2.TIP
unnamed: C5.2, C7.2, C8.2
unnamed: C7.1, C8.1, IC4.3 (VOUT), POWER_SELECT.1
RST: C6.2, IC2.1 (OE), IC2.2 (I), IC3.29 (PC6(/RESET/PCINT14)), ICSP.5 (RST), R3.2, R4.2, S1.3, S1.4 (P1)
RTS: XBEE.16 (RTS/AD6/DIO6)
RTS#: C6.1, JP7.6
RXD: IC3.30 (PD0(RXD/PCINT16)), JP7.4
SCK: IC3.17 (PB5(SCK/PCINT5)), ICSP.3 (SCK), R5.1
TXD: IC3.31 (PD1(TXD/PCINT17)), JP7.5
USB_5V: JP7.3, POWER_SELECT.3
VCC: C10.1, IC2.14 (VCC), IC6.3 (VOUT), R3.1, R7.1, XBEE.1 (VCC)

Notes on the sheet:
DTR
RST
RTS
CTS
v1.2
Design based on http://www.ladyada.net/make/boarduino
Creative Commons 3.0
Attribution/Share-Alike
I2C
ICSP
Power Supply
LD2915050
LD1117ADT33TR

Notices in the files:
parts and their libraries:
SparkFun-Electromechanical: Licensing: CC v3.0 Share-Alike You are welcome to use this library for commercial purposes.
